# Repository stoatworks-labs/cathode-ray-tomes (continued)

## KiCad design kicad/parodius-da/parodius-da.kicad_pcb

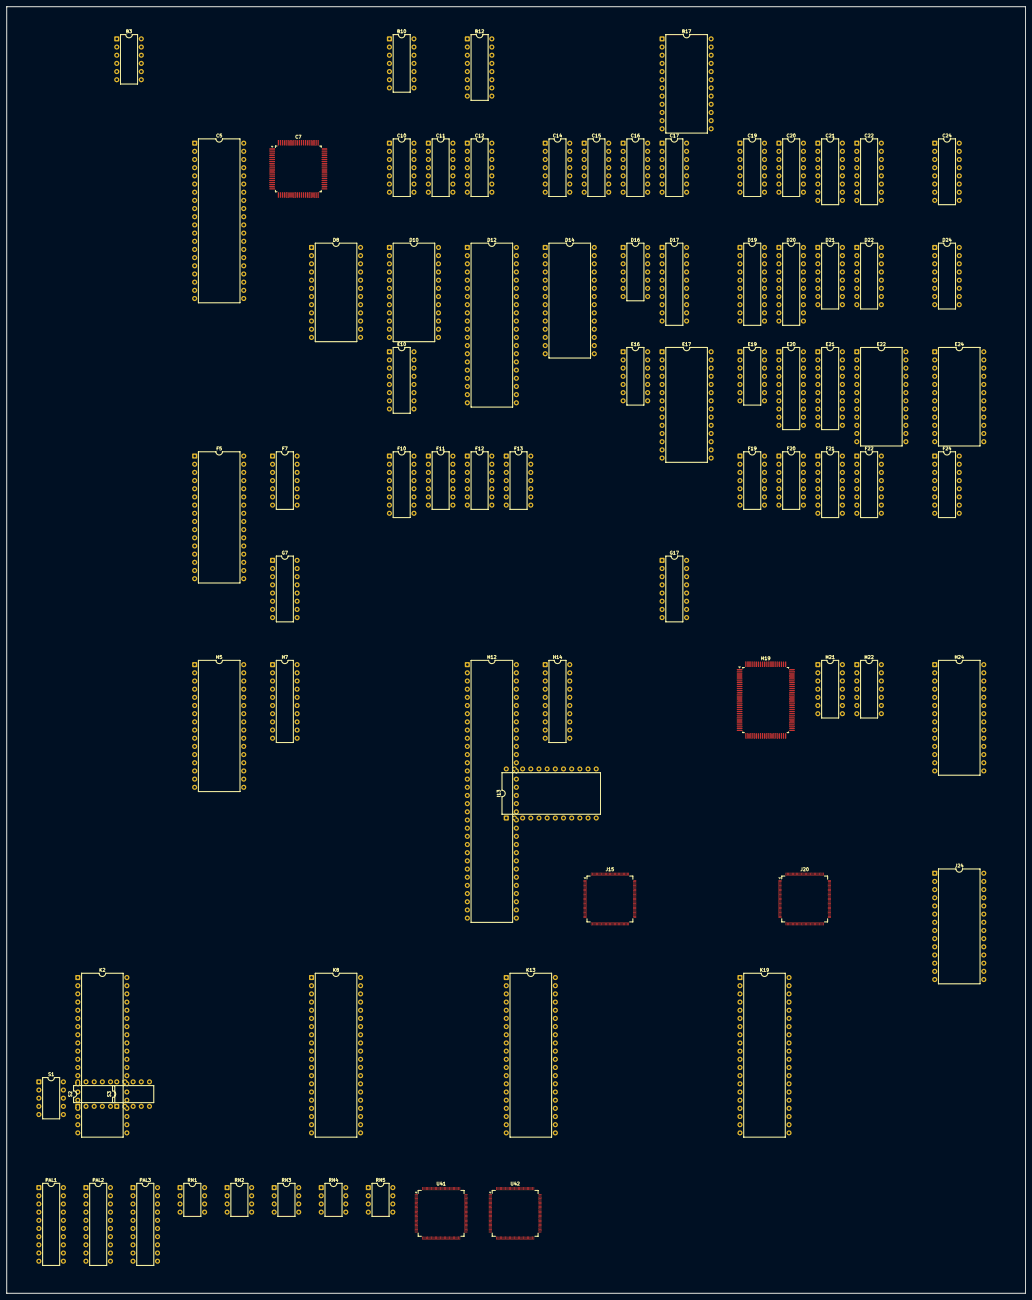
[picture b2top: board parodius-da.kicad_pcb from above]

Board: 2 copper layers, 316.5 x 399.7 mm, 79 parts (0 on the bottom side), 541 nets, no tracks yet.

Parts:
B3: MB3722; DIP-12_W7.62mm
B10: LM324; DIP-14_W7.62mm
B12: YM3012; DIP-16_W7.62mm
B17: 051550; DIP-24_W15.24mm
C5: 955D04; DIP-40_W15.24mm
C7: 053260; PQFP-80_14x14mm_P0.65mm
C10: 74LS32; DIP-14_W7.62mm
C11: 74LS74; DIP-14_W7.62mm
C12: 74LS20; DIP-14_W7.62mm
C14: 74LS04; DIP-14_W7.62mm
C15, C16, C17, C19, C20: 74LS07; DIP-14_W7.62mm
C21, C22, C24: 74LS253; DIP-16_W7.62mm
D8: YM2151; DIP-24_W15.24mm
D10: CY7C128-45PC; DIP-24_W15.24mm
D12: Z80CPU; DIP-40_W15.24mm
D14: 27C512; DIP-28_W15.24mm
D16: 74LS74; DIP-14_W7.62mm
D17, D19, D20: 74LS273; DIP-20_W7.62mm
D21: 74LS253; DIP-16_W7.62mm
D22, D24: 74LS257; DIP-16_W7.62mm
E10: 74LS139; DIP-16_W7.62mm
E16: 74LS00; DIP-14_W7.62mm
E17: MB8464A-10W-15W; DIP-28_W15.24mm
E19: 74LS07; DIP-14_W7.62mm
E20, E21: 74LS245; DIP-20_W7.62mm
E22, E24: HM6116P-3; DIP-24_W15.24mm
F5: 27C010; DIP-32_W15.24mm
F7: 74LS04; DIP-14_W7.62mm
F10: 74LS367; DIP-16_W7.62mm
F11: 74LS08; DIP-14_W7.62mm
F12, F13: 74LS32; DIP-14_W7.62mm
F19: 74LS74; DIP-14_W7.62mm
F20: 74LS164; DIP-14_W7.62mm
F21, F22, F24: 74LS157; DIP-16_W7.62mm
G7: 74LS174; DIP-16_W7.62mm
G17: 74LS157; DIP-16_W7.62mm
H5: 27C010; DIP-32_W15.24mm
H7, H14: 74LS245; DIP-20_W7.62mm
H12: 053248; DIP-64_W15.24mm
H19: 053251; PQFP-100_14x20mm_P0.65mm
H21: 74LS04; DIP-14_W7.62mm
H22: 74LS74; DIP-14_W7.62mm
H24: MB8464A-10W-15W; DIP-28_W15.24mm
I13: HM6116P-3; DIP-24_W15.24mm
J15: 051962; TQFP-120_14x14mm_P0.4mm
J20: 052109; TQFP-120_14x14mm_P0.4mm
J24: MB8464A-10W-15W; DIP-28_W15.24mm
K2, K8, K13, K19: 955D05-06-07-08; DIP-40_W15.24mm
PAL1, PAL2, PAL3: PAL16L8; DIP-20_W7.62mm
RN1, RN2, RN3, RN4, RN5: KONAMI_005273; DIP-8_W7.62mm
S1, S2, S3: 052535; DIP-10_W7.62mm
U41: 053245; TQFP-120_14x14mm_P0.4mm
U42: 053244; TQFP-120_14x14mm_P0.4mm

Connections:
/+12V: B3.10, B17.19
/AUX1: C7.23, D8.21
/COIN_CNT_1: B17.22, B17.23
/COIN_CNT_2: B17.20, B17.21
/CPU~EN: D22.2, F13.9, U41.26
/DFI0: H19.47, J15.59
/DFI1: H19.48, J15.60
/DFI2: H19.49, J15.62
/DFI3: H19.50, J15.63
/DFI5: H19.51, J15.65
/DFI6: H19.52, J15.66
/DFI7: H19.54, J15.67
/DSA0: H19.66, J15.46
/DSA1: H19.67, J15.47
/DSA2: H19.68, J15.48
/DSA3: H19.69, J15.49
/DSA5: H19.70, J15.51
/DSA6: H19.71, J15.52
/DSA7: H19.72, J15.53
/DSB0: H19.57, J15.30
/DSB1: H19.58, J15.32
/DSB2: H19.59, J15.33
/DSB3: H19.60, J15.34
/DSB5: H19.61, J15.36
/DSB6: H19.62, J15.37
/DSB7: H19.63, J15.38
/GM12: J15.95, U41.12, U42.12
/IOCS: D22.15, D24.15, PAL1.13
/M6: D16.3, D19.11, D20.11, F20.8, H19.41, J15.78, U41.10, U42.10
/M12: F19.3, H21.11, H21.13, J20.103
/MAIN_A0: C7.18, E17.10, F5.12, F7.5, F7.9, G17.11, H5.12, H12.14, H19.85, J15.88, J20.66, U41.9, U42.19
/MAIN_A1: E17.9, F5.11, F7.11, F24.2, H5.11, H12.13, H19.84, J15.89, J20.67, U41.25, U42.18
/MAIN_A2: E10.14, E17.8, F5.10, F24.5, H5.10, H12.12, H19.83, J20.68, U41.24, U42.17
/MAIN_A3: E10.13, E17.7, F5.9, F24.11, H5.9, H12.11, H19.82, J20.69, U41.23, U42.15
/MAIN_A4: E17.6, F5.8, F24.14, H5.8, H12.9, J20.116, PAL1.11, U41.22
/MAIN_A5: E17.5, F5.7, F22.2, H5.7, H12.8, J20.115, PAL1.9, U41.20
/MAIN_A6: E17.4, F5.6, F22.5, H5.6, H12.7, J20.114, PAL1.8, U41.19
/MAIN_A7: E17.3, F5.5, F22.11, H5.5, H12.6, J20.113, PAL1.5, U41.18
/MAIN_A8: E17.25, F5.27, F22.14, H5.27, H12.62, J20.112, PAL1.4, U41.17
/MAIN_A9: E17.24, F5.26, F21.2, H5.26, H12.61, J20.111, PAL1.3, U41.15
/MAIN_A10: E17.21, F5.23, F21.5, H5.23, H12.60, J20.110, PAL3.8, U41.14
/MAIN_A11: E17.23, F5.25, H5.25, H12.59, J20.109, PAL3.7
/MAIN_A12: E17.2, F5.4, H5.4, H12.56, J20.80, PAL3.6
/MAIN_A13: H12.55, J20.81, PAL2.5, PAL3.5
/MAIN_A14: H12.54, J20.82, PAL2.4, PAL3.4
/MAIN_A15: H12.53, J20.83, PAL2.3, PAL3.3
/MAIN_A16: H12.38, PAL2.9
/MAIN_A17: H12.39, PAL2.8
/MAIN_A18: H12.40, PAL2.7
/MAIN_A19: H12.41, PAL2.6
/MAIN_DB0: C7.8, C24.7, D17.3, D22.4, E17.11, E20.2, E21.2, G7.3, H7.2, H14.2, H19.80, J15.79, J20.56, U42.29
/MAIN_DB1: C7.9, C24.9, D17.4, D22.7, E17.12, E20.3, E21.3, G7.4, H7.3, H14.3, H19.79, J15.80, J20.57, U42.28
/MAIN_DB2: C7.10, C22.7, D17.7, D22.9, E17.13, E20.4, E21.4, G7.6, H7.4, H14.4, H19.77, J15.81, J20.58, U42.27
/MAIN_DB3: C7.11, C22.9, D17.8, D22.12, E17.15, E20.5, E21.5, H7.5, H14.5, H19.76, J15.82, J20.59, U42.26
/MAIN_DB4: C7.13, C21.7, D17.13, D24.4, E17.16, E20.6, E21.6, H7.6, H14.6, H19.75, J15.83, J20.60, U42.25
/MAIN_DB5: C7.14, C21.9, D17.14, D24.7, E17.17, E20.7, E21.7, G7.11, H7.7, H14.7, H19.74, J15.84, J20.62, U42.24
/MAIN_DB6: C7.15, D17.17, D21.7, D24.9, E17.18, E20.8, E21.8, G7.13, H7.8, J15.85, J20.63, U42.23
/MAIN_DB7: C7.16, D17.18, D21.9, D24.12, E17.19, E20.9, E21.9, G7.14, H7.9, H14.8, H14.9, J15.86, J20.64, U42.22
/MAIN~IRQ: H12.4, J20.87
/MBRIT0: D17.15, E16.5
/MBRIT1: D17.16, E16.13
/MBRIT2: D17.19, E16.2
/OBJPXL0: H19.30, U42.120
/OBJPXL1: H19.31, U42.119
/OBJPXL2: H19.32, U42.118
/OBJPXL3: H19.33, U42.117
/OBJPXL4: H19.34, U42.116
/OBJPXL5: H19.35, U42.115
/OBJPXL6: H19.36, U42.114
/OBJPXL7: H19.37, U42.113
/OBJPXL8: H19.38, U42.112
/PALETTE~CS: E20.1, E21.1, F11.5, F21.1, F21.14, F22.1, F24.1, G17.1, PAL3.14
/PAL_BANK: F21.11, G7.7
/PQ: F10.4, J20.89
/PR13: H19.25, U42.110
/PR14: H19.27, U42.109
/RMSCR~RD: D17.9, J15.96, J20.97, PAL1.2
/R/~W: C7.19, E17.27, F7.3, F12.2, F12.9, F12.13, H7.1, H12.15
/SCR_PE: F10.2, F19.11, J20.90
/SC~CS: C7.72, E10.6
/SDI0: H19.95, U42.108
/SH1: B12.6, C7.22, C11.11, D8.20
/SH2: B12.5, D8.19
/SND_A0: C7.70, D8.4, D10.8, D12.30, D14.10
/SND_A1: C7.69, D10.7, D12.31, D14.9
/SND_A2: C7.68, D10.6, D12.32, D14.8
/SND_A3: C7.67, D10.5, D12.33, D14.7
/SND_A4: C7.66, D10.4, D12.34, D14.6
/SND_A5: C7.65, D10.3, D12.35, D14.5
/SND_A6: D10.2, D12.36, D14.4
/SND_A7: D10.1, D12.37, D14.3
/SND_A8: D10.23, D12.38, D14.25
/SND_A9: D10.22, D12.39, D14.24, E10.2
/SND_A10: D10.19, D12.40, D14.21, E10.3
/SND_A11: C10.10, C14.1, D12.1, D14.23
/SND_A12: C12.5, D12.2, D14.2
/SND_A13: C12.4, D12.3, D14.26
/SND_A14: C12.2, D12.4, D14.27
/SND_A15: C12.1, D12.5, D14.1
/SND_D0: C7.5, D8.10, D10.9, D12.14, D14.11
/SND_D1: C7.4, D8.12, D10.10, D12.15, D14.12
/SND_D2: C7.3, D8.13, D10.11, D12.12, D14.13
/SND_D3: C7.2, D8.14, D10.13, D12.8, D14.15
/SND_D4: C7.1, D8.15, D10.14, D12.7, D14.16
/SND_D5: C7.80, D8.16, D10.15, D12.9, D14.17
/SND_D6: C7.79, D8.17, D10.16, D12.10, D14.18
/SND_D7: C7.78, D8.18, D10.17, D12.13, D14.19
/SO~CLK: B12.2, D8.23
/S~CLK: C7.21, D8.24, D12.6, F7.12
/S~RD: D8.6, D10.20, D12.21, D14.22, F7.1
/WD_OUT1: B17.15, D17.2
/WD_OUT2: B17.16, D17.5
/colmix/BRIT: D16.2, H19.88
/colmix/BRITEN: D16.5, E16.1, E16.4, E16.12
/colmix/CO1: F24.3, H19.19
/colmix/CO2: F24.6, H19.18
/colmix/CO3: F24.10, H19.17
/colmix/CO4: F24.13, H19.16
/colmix/CO5: F22.3, H19.14
/colmix/CO6: F22.6, H19.13
/colmix/CO7: F22.10, H19.12
/colmix/CO8: F22.13, H19.11
/colmix/CO9: F21.3, H19.93
/colmix/CO10: F21.6, H19.92
/colmix/CO11: F21.10, H19.91
/colmix/MCO1: E22.19, E24.8, F24.4
/colmix/MCO2: E22.8, E24.7, F24.7
/colmix/MCO3: E22.5, E24.6, F24.9
/colmix/MCO4: E22.4, E24.5, F22.4
/colmix/MCO5: E22.6, E24.4, F22.12
/colmix/MCO6: E22.7, E24.3, F21.7
/colmix/MCO7: E22.23, E24.2, F21.9
/colmix/MCO8: E22.22, E24.1, F24.12
/colmix/MCO9: E22.1, E24.23, F22.9
/colmix/MCO10: E22.2, E24.22, F21.4
/colmix/MCO11: E22.3, E24.19, F22.7
/colmix/MCO~OE: E22.20, E24.20, F21.12
/colmix/MCO~WRH: E24.21, F13.6
/colmix/MCO~WRL: E22.21, F13.3
/colmix/RGB0: D19.3, E21.18, E22.9
/colmix/RGB1: D19.4, E21.17, E22.10
/colmix/RGB2: D19.7, E21.16, E22.11
/colmix/RGB3: D19.8, E21.15, E22.13
/colmix/RGB4: D19.13, E21.14, E22.14
/colmix/RGB5: D19.14, E21.13, E22.15
/colmix/RGB6: D19.17, E21.12, E22.16
/colmix/RGB7: E21.11, E22.17
/colmix/RGB8: D20.3, E20.18, E24.9
/colmix/RGB9: D20.4, E20.17, E24.10
/colmix/RGB10: D20.7, E20.16, E24.11
/colmix/RGB11: D20.8, E20.15, E24.13
/colmix/RGB12: D20.13, E20.14, E24.14
/colmix/RGB13: D20.14, E20.13, E24.15
/colmix/RGB14: D20.17, E20.12, E24.16
/colmix/RGB15: D20.18, E20.11, E24.17
/colmix/SDO0: C14.5, H19.87
/colmix/rgb/B0: C17.5, D19.6
/colmix/rgb/B1: C16.11, D19.9
/colmix/rgb/B2: C16.9, D19.12
/colmix/rgb/B3: C15.9, D19.15
/colmix/rgb/B4: C15.11, D19.16
/colmix/rgb/G0: C17.9, D20.15
/colmix/rgb/G1: C19.3, D20.16
/colmix/rgb/G2: C20.13, D20.19
/colmix/rgb/G3: C19.5, D19.2
/colmix/rgb/G4: C17.3, D19.5
/colmix/rgb/R0: C20.9, D20.2
/colmix/rgb/R1: C20.1, D20.5
/colmix/rgb/R2: C20.5, D20.6
/colmix/rgb/R3: C20.3, D20.9
/colmix/rgb/R4: C20.11, D20.12
/colmix/rgb/~MBRIT0: E16.6, E19.1, E19.11, E19.13
/colmix/rgb/~MBRIT1: C19.1, C19.11, C19.13, E16.11
/colmix/rgb/~MBRIT2: C17.1, C17.11, C17.13, E16.3
/colmix/rgb/~SHADOW: C16.1, C16.3, C16.13, D19.19
/colmix/~COCEH: E20.19, F13.4, G17.12
/colmix/~COCEL: E21.19, F13.1, G17.9
/colmix/~CS: F12.11, H19.81
/io_cabinet/I1P_BTN_1: C21.13, RN5.5
/io_cabinet/I1P_BTN_2: D21.3, RN1.1
/io_cabinet/I1P_BTN_3: D21.13, RN1.5
/io_cabinet/I1P_DOWN: C22.3, RN3.1
/io_cabinet/I1P_LEFT: C22.13, RN3.5
/io_cabinet/I1P_RIGHT: C21.3, RN5.1
/io_cabinet/I1P_START: C24.3, RN2.1
/io_cabinet/I1P_UP: C24.13, RN2.5
/io_cabinet/I2P_BTN_1: C21.12, RN5.7
/io_cabinet/I2P_BTN_2: D21.4, RN1.3
/io_cabinet/I2P_BTN_3: D21.12, RN1.7
/io_cabinet/I2P_DOWN: C22.4, RN3.3
/io_cabinet/I2P_LEFT: C22.12, RN3.7
/io_cabinet/I2P_RIGHT: C21.4, RN5.3
/io_cabinet/I2P_START: C24.4, RN2.3
/io_cabinet/I2P_UP: C24.12, RN2.7
/io_cabinet/ICOIN_1: C22.5, RN4.5
/io_cabinet/ICOIN_2: C22.11, RN4.7
/io_cabinet/ISERVICE1: C24.5, RN4.1
/io_cabinet/ISERVICE2: C24.11, RN4.3
/io_cabinet/~A0: C21.14, C22.14, C24.14, D21.14, D22.1, D24.1, F7.6
/io_cabinet/~A1: C21.2, C22.2, C24.2, D21.2, F7.10
/main/AS: F19.4, F19.10, H21.4, H22.1
/main/BANK1: G7.5, PAL3.9
/main/BANKR: D17.12, PAL3.2
/main/BANK~CS: E10.11, G7.9
/main/DTAC: F11.6, H12.49
/main/GND: F5.16, H5.16, PAL1.10
/main/MAIN_A20: H12.43, PAL2.18
/main/MAIN_D0: F5.13, H5.13, H7.18, H12.21
/main/MAIN_D1: F5.14, H5.14, H7.17, H12.22
/main/MAIN_D2: F5.15, H5.15, H7.16, H12.23
/main/MAIN_D3: F5.17, H5.17, H7.15, H12.24
/main/MAIN_D4: F5.18, H5.18, H7.14, H12.27
/main/MAIN_D5: F5.19, H5.19, H7.13, H12.28
/main/MAIN_D6: F5.20, H5.20, H7.12, H12.29
/main/MAIN_D7: F5.21, H5.21, H7.11, H12.30
/main/MAIN~CLK: H12.18, H21.12
/main/MAIN~RST: F10.7, H12.2
/main/MISC: E10.15, PAL1.14
/main/MPQ: F10.5, H12.17
/main/NC: PAL2.1, PAL3.18
/main/PE: F10.3, H12.51
/main/PROG_A13: F5.28, H5.28, PAL2.12
/main/PROG_A14: F5.29, H5.29, PAL2.13
/main/PROG_A15: F5.3, H5.3, PAL2.14
/main/PROG_A16: F5.2, H5.2, PAL2.15
/main/WORK~CS: E17.20, PAL3.16
/main/~AS: F19.12, H12.16, H21.3, PAL3.1
/main/~M12: H21.10, H22.3
/main/~PAGED: E16.10, PAL2.11, PAL3.17
/main/~PROGCS1: F5.24, PAL2.17
/main/~PROGCS2: E16.9, H5.24, PAL2.16
/main/~UNPAGED: PAL2.2, PAL3.19
/main/~WRK: G7.2, PAL3.11
/main/~i6: PAL1.6, PAL3.13
/main/~i7: PAL1.7, PAL3.12
/objects/AR0: U41.119, U42.30
/objects/AR1: U41.118, U42.32
/objects/AR2: U41.117, U42.33
/objects/AROK: U41.116, U42.34
/objects/BR0: U41.115, U42.35
/objects/BR1: U41.114, U42.36
/objects/BR2: U41.113, U42.37
/objects/BROK: U41.112, U42.38
/objects/CLAT: U41.86, U42.64
/objects/HP0: U41.96, U42.54
/objects/HP1: U41.97, U42.53
/objects/HP2: U41.98, U42.52
/objects/HP3: U41.99, U42.50
/objects/HP4: U41.100, U42.49
/objects/HP5: U41.102, U42.48
/objects/HP6: U41.103, U42.47
/objects/HP7: U41.104, U42.45
/objects/HP8: U41.105, U42.44
/objects/HP9: U41.107, U42.43
/objects/HRFP: U41.110, U42.39
/objects/OBJRAMD0: H14.18, I13.9, U41.45
/objects/OBJRAMD1: H14.17, I13.10, U41.44
/objects/OBJRAMD2: H14.16, I13.11, U41.43
/objects/OBJRAMD3: H14.15, I13.13, U41.42
/objects/OBJRAMD4: H14.14, I13.14, U41.40
/objects/OBJRAMD5: H14.13, I13.15, U41.39
/objects/OBJRAMD6: H14.12, I13.16, U41.38
/objects/OBJRAMD7: H14.11, I13.17, U41.37
/objects/OBJROMA0: K2.9, K8.9, U41.85
/objects/OBJROMA1: K2.8, K8.8, U41.84
/objects/OBJROMA2: K2.7, K8.7, U41.83
/objects/OBJROMA3: K2.6, K8.6, U41.82
/objects/OBJROMA4: K2.5, K8.5, U41.80
/objects/OBJROMA5: K2.4, K8.4, U41.79
/objects/OBJROMA6: K2.3, K8.3, U41.78
/objects/OBJROMA7: K2.2, K8.2, U41.77
/objects/OBJROMA8: K2.40, K8.40, U41.75
/objects/OBJROMA9: K2.39, K8.39, U41.74
/objects/OBJROMA10: K2.38, K8.38, U41.73
/objects/OBJROMA11: K2.37, K8.37, U41.72
/objects/OBJROMA12: K2.36, K8.36, U41.70
/objects/OBJROMA13: K2.35, K8.35, U41.69
/objects/OBJROMA14: K2.34, K8.34, U41.68
/objects/OBJROMA15: K2.33, K8.33, U41.67
/objects/OBJROMA16: K2.32, K8.32, U41.66
/objects/OBJROMA17: K2.1, K8.1, U41.65
/objects/OBJROMD0: K2.13, U42.100
/objects/OBJROMD1: K2.15, U42.99
/objects/OBJROMD2: K2.17, U42.98
/objects/OBJROMD3: K2.19, U42.97
/objects/OBJROMD4: K2.22, U42.96
/objects/OBJROMD5: K2.24, U42.95
/objects/OBJROMD6: K2.26, U42.94
/objects/OBJROMD7: K2.28, U42.93
/objects/OBJROMD8: K2.14, U42.92
/objects/OBJROMD9: K2.16, U42.90
/objects/OBJROMD10: K2.18, U42.89
/objects/OBJROMD11: K2.20, U42.88
/objects/OBJROMD12: K2.23, U42.87
/objects/OBJROMD13: K2.25, U42.86
/objects/OBJROMD14: K2.27, U42.85
/objects/OBJROMD15: K2.29, U42.84
/objects/OBJROMD16: K8.13, U42.83
/objects/OBJROMD17: K8.15, U42.82
/objects/OBJROMD18: K8.17, U42.80
/objects/OBJROMD19: K8.19, U42.79
/objects/OBJROMD20: K8.22, U42.78
/objects/OBJROMD21: K8.24, U42.77
/objects/OBJROMD22: K8.26, U42.75
/objects/OBJROMD23: K8.28, U42.74
/objects/OBJROMD24: K8.14, U42.73
/objects/OBJROMD25: K8.16, U42.72
/objects/OBJROMD26: K8.18, U42.70
/objects/OBJROMD27: K8.20, U42.69
/objects/OBJROMD28: K8.23, U42.68
/objects/OBJROMD29: K8.25, U42.67
/objects/OBJROMD30: K8.27, U42.66
/objects/OBJROMD31: K8.29, U42.65
/objects/ORAMA0: I13.3, U41.50
/objects/ORAMA1: I13.4, U41.52
/objects/ORAMA2: I13.5, U41.53
/objects/ORAMA3: I13.23, U41.54
/objects/ORAMA4: I13.6, U41.55
/objects/ORAMA5: I13.22, U41.56
/objects/ORAMA6: I13.7, U41.57
/objects/ORAMA7: I13.8, U41.58
/objects/ORAMA8: I13.19, U41.59
/objects/ORAMA9: I13.2, U41.62
/objects/ORAMA10: I13.1, U41.63
/objects/PL0: U41.87, U42.63
/objects/PL1: U41.88, U42.62
/objects/PL2: U41.89, U42.60
/objects/PL3: U41.90, U42.59
/objects/PL4: U41.92, U42.58
/objects/PL5: U41.93, U42.57
/objects/PL6: U41.94, U42.56
/objects/SHADOW: U41.95, U42.55
/objects/~HIT: U41.108, U42.42
/objects/~OBJRAM_RD: F13.11, H14.1
/objects/~ZLD: U41.109, U42.40
/pcm/RA0: C5.29, C7.39
/pcm/RA1: C5.9, C7.40
/pcm/RA2: C5.8, C7.41
/pcm/RA3: C5.7, C7.42
/pcm/RA4: C5.6, C7.44
/pcm/RA5: C5.5, C7.45
/pcm/RA6: C5.4, C7.46
/pcm/RA7: C5.3, C7.47
/pcm/RA8: C5.2, C7.48
/pcm/RA9: C5.40, C7.49
/pcm/RA10: C5.39, C7.50
/pcm/RA11: C5.38, C7.51
/pcm/RA12: C5.37, C7.53
/pcm/RA13: C5.36, C7.54
/pcm/RA14: C5.35, C7.55
/pcm/RA15: C5.34, C7.56
/pcm/RA16: C5.33, C7.57
/pcm/RA17: C5.32, C7.58
/pcm/RA18: C5.1, C7.59
/pcm/RD0: C5.13, C7.29
/pcm/RD1: C5.15, C7.30
/pcm/RD2: C5.17, C7.31
/pcm/RD3: C5.19, C7.32
/pcm/RD4: C5.22, C7.35
/pcm/RD5: C5.24, C7.36
/pcm/RD6: C5.26, C7.37
/pcm/RD7: C5.28, C7.38
/scroll/COL5: J15.109, J20.42
/scroll/COL6: J15.108, J20.43
/scroll/COL7: J15.107, J20.46
/scroll/GFXROMA0: J20.35, K13.9, K19.9
/scroll/GFXROMA1: J20.34, K13.8, K19.8
/scroll/GFXROMA2: J20.33, K13.7, K19.7
/scroll/GFXROMA3: J20.32, K13.6, K19.6
/scroll/GFXROMA4: J20.30, K13.5, K19.5
/scroll/GFXROMA5: J20.29, K13.4, K19.4
/scroll/GFXROMA6: J20.28, K13.3, K19.3
/scroll/GFXROMA7: J20.27, K13.2, K19.2
/scroll/GFXROMA8: J20.26, K13.40, K19.40
/scroll/GFXROMA9: J20.25, K13.39, K19.39
/scroll/GFXROMA10: J20.24, K13.38, K19.38
/scroll/GFXROMA11: J20.37, K13.37, K19.37
/scroll/GFXROMA12: J20.38, K13.36, K19.36
/scroll/GFXROMA13: J20.41, K13.35, K19.35
/scroll/GFXROMA14: J20.39, K13.34, K19.34
/scroll/GFXROMA15: J20.40, K13.33, K19.33
/scroll/GFXROMA16: J20.23, K13.32, K19.32
/scroll/GFXROMA17: J20.22, K13.1, K19.1
/scroll/GFXROMD0: J15.29, K13.13
/scroll/GFXROMD1: J15.28, K13.15
/scroll/GFXROMD2: J15.27, K13.17
/scroll/GFXROMD3: J15.26, K13.19
/scroll/GFXROMD4: J15.25, K13.22
/scroll/GFXROMD5: J15.24, K13.24
/scroll/GFXROMD6: J15.23, K13.26
/scroll/GFXROMD7: J15.22, K13.28
/scroll/GFXROMD8: J15.21, K13.14
/scroll/GFXROMD9: J15.20, K13.16
/scroll/GFXROMD10: J15.19, K13.18
/scroll/GFXROMD11: J15.18, K13.20
/scroll/GFXROMD12: J15.17, K13.23
/scroll/GFXROMD13: J15.16, K13.25
/scroll/GFXROMD14: J15.13, K13.27
/scroll/GFXROMD15: J15.12, K13.29
/scroll/GFXROMD16: J15.11, K19.13
/scroll/GFXROMD17: J15.10, K19.15
/scroll/GFXROMD18: J15.9, K19.17
/scroll/GFXROMD19: J15.8, K19.19
/scroll/GFXROMD20: J15.7, K19.22
/scroll/GFXROMD21: J15.6, K19.24
/scroll/GFXROMD22: J15.5, K19.26
/scroll/GFXROMD23: J15.4, K19.28
/scroll/GFXROMD24: J15.3, K19.14
/scroll/GFXROMD25: J15.2, K19.16
/scroll/GFXROMD26: J15.120, K19.18
/scroll/GFXROMD27: J15.119, K19.20
/scroll/GFXROMD28: J15.118, K19.23
/scroll/GFXROMD29: J15.117, K19.25
/scroll/GFXROMD30: J15.116, K19.27
/scroll/GFXROMD31: J15.115, K19.29
/scroll/M24: H21.6, J15.90, J20.65
/scroll/SCRAMA0: H24.10, J20.2, J24.10
/scroll/SCRAMA1: H24.9, J20.120, J24.9
/scroll/SCRAMA2: H24.8, J20.119, J24.8
/scroll/SCRAMA3: H24.7, J20.118, J24.7
/scroll/SCRAMA4: H24.6, J20.117, J24.6
/scroll/SCRAMA5: H24.5, J20.70, J24.5
/scroll/SCRAMA6: H24.4, J20.71, J24.4
/scroll/SCRAMA7: H24.3, J20.72, J24.3
/scroll/SCRAMA8: H24.25, J20.73, J24.25
/scroll/SCRAMA9: H24.24, J20.76, J24.24
/scroll/SCRAMA10: H24.21, J20.77, J24.21
/scroll/SCRAMA11: H24.23, J20.78, J24.23
/scroll/SCRAMA12: H24.2, J20.79, J24.2
/scroll/VD0: H24.11, J20.20
/scroll/VD1: H24.12, J20.19
/scroll/VD2: H24.13, J20.18
/scroll/VD3: H24.15, J20.17
/scroll/VD4: H24.16, J20.16
/scroll/VD5: H24.17, J20.13
/scroll/VD6: H24.18, J20.12
/scroll/VD7: H24.19, J20.11
/scroll/VD8: J20.10, J24.11
/scroll/VD9: J20.9, J24.12
/scroll/VD10: J20.8, J24.13
/scroll/VD11: J20.7, J24.15
/scroll/VD12: J20.6, J24.16
/scroll/VD13: J20.5, J24.17
/scroll/VD14: J20.4, J24.18
/scroll/VD15: J20.3, J24.19
/scroll/ZA1H: J15.101, J20.50
/scroll/ZA2H: J15.100, J20.51
/scroll/ZA4H: J15.99, J20.52
/scroll/ZB1H: J15.106, J20.47
/scroll/ZB2H: J15.103, J20.48
/scroll/ZB4H: J15.102, J20.49
/scroll/~BE: J15.98, J20.53
/scroll/~RCS1: J20.93, J24.20
/scroll/~ROE1: J20.95, J24.22
/scroll/~ROE2: H24.22, J20.96
/scroll/~RWE1: J20.107, J24.27
/scroll/~RWE2: H24.27, J20.108
/sound/SND~E: C10.11, E10.1
/sound/SRAM~CE: C10.8, D10.18
/sound/SROM~CE: C14.8, D14.20
/sound/S~IORQ: D12.20, F11.2
/sound/S~MREQ: C10.5, D12.19
/sound/S~WR: D8.5, D10.21, D12.22
/sound/~RFSH: C14.13, D12.28
/sound/~SET: C11.10, E10.5
/~HBLANK: F20.2, J15.70
/~HSYNC: J15.73, U41.4, U42.8
/~JOYSTK: C21.1, C21.15, C22.1, C22.15, C24.1, C24.15, D21.1, D21.15, PAL1.12
/~MDS: F13.2, F13.5, H12.20, U42.14
/~OBJRAM_CS: F11.12, F12.10, PAL3.15
/~OBJSET: C14.11, F11.13, PAL1.17, U41.6, U42.13
/~OUTCS: E10.12, F12.1, F12.4
/~PCU_CS: F12.12, PAL1.16
/~RCS0: J20.92, U41.3, U42.3
/~RD: E17.22, F7.4, F12.5, F13.12, J15.87, J20.85, U41.13, U42.20
/~RESET: D17.1, F10.6, G7.1, J20.98
/~SOON: D16.11, E10.10
/~SOREG: C7.17, E10.9
/~VBLANK: F20.1, J15.69
/~VCS: H22.2, J15.97, J20.54, J20.84, PAL1.18
/~VSYNC: J15.72, U41.5, U42.9
/~WDOGRST: B12.7, C7.75, C11.13, D8.3, D12.26, F11.1, F20.9, H22.9, J15.92, J20.55
/~WDRST: B17.10, H22.12, H22.13
unnamed: B10.3, B12.15
unnamed: B10.2, B12.14
unnamed: B10.5, B12.9
unnamed: B10.6, B10.7
unnamed: B10.10, B12.12
unnamed: B10.8, B10.9
unnamed: B10.12, B12.10
unnamed: B10.13, B10.14
unnamed: B10.1, B12.13
unnamed: B17.1, F12.6
unnamed: C7.71, F7.2
unnamed: C10.1, C14.12
unnamed: C10.2, C12.6, C14.9
unnamed: C10.3, C10.4
unnamed: C10.6, C10.9, C10.12
unnamed: C10.13, C14.2
unnamed: C11.9, D12.17
unnamed: C14.10, F13.13
unnamed: D8.7, E10.4
unnamed: D12.16, D16.8
unnamed: D16.13, F11.3
unnamed: D17.11, F12.3
unnamed: C14.6, D19.18
unnamed: F11.11, F13.10
unnamed: F11.8, F19.2
unnamed: F11.4, F19.5
unnamed: F11.9, F19.9
unnamed: C15.1, C15.3, C15.13, F20.5
unnamed: F7.8, G17.14
unnamed: H21.1, H21.5
unnamed: E16.8, H7.19
unnamed: F13.8, H14.19
unnamed: F11.10, H22.6
unnamed: H21.2, H22.11
unnamed: I13.20, U41.49
unnamed: I13.21, U41.47
unnamed: C15.5, J15.76
unnamed: C15.2, S1.7
unnamed: C17.6, S1.6
unnamed: C16.10, S1.5
unnamed: C16.8, S1.4
unnamed: C15.8, S1.3
unnamed: C15.10, S1.2
unnamed: C15.12, S2.7
unnamed: C17.8, S2.6
unnamed: C19.4, S2.5
unnamed: C20.12, S2.4
unnamed: C19.6, S2.3
unnamed: C17.4, S2.2
unnamed: C15.4, S3.7
unnamed: C20.8, S3.6
unnamed: C20.2, S3.5
unnamed: C20.6, S3.4
unnamed: C20.4, S3.3
unnamed: C20.10, S3.2
unnamed: F12.8, U41.7
VCC: B10.4, B12.1, B17.9, C5.21, C7.20, C7.33, C7.73, C10.14, C11.14, C12.14, C14.14, C15.14, C16.14, C17.14, C19.14, C20.14, C21.16, C22.16, C24.16, D8.22, D10.24, D12.11, D14.28, D16.1, D16.4, D16.10, D16.12, D16.14, D19.1, D20.1, D21.16, D24.2, D24.5, D24.11, D24.14, E10.16, E16.14, E17.26, E17.28, E19.14, E22.24, E24.24, F5.1, F5.31, F5.32, F7.14, F10.16, F11.14, F12.14, F13.14, F19.1, F19.13, F19.14, F20.14, G7.16, G17.10, G17.13, H5.1, H5.31, H5.32, H12.26, H12.50, H12.58, H19.1, H19.2, H19.3, H19.28, H19.29, H19.39, H19.42, H19.43, H19.44, H19.45, H19.46, H19.53, H19.78, H19.97, H19.98, H19.99, H19.100, H21.14, H22.4, H22.10, H22.14, H24.26, H24.28, I13.24, J15.14, J15.44, J15.74, J15.104, J20.14, J20.44, J20.74, J20.104, J24.26, J24.28, K2.21, K2.31, K8.21, K8.31, K13.21, K13.31, K19.21, K19.31, PAL1.1, PAL1.20, PAL2.20, PAL3.20, S1.1, S2.1, S3.1, U41.16, U41.46, U41.60, U41.76, U41.106, U41.120, U42.16, U42.46, U42.76, U42.106
VSS: B3.6, B3.7, B10.11, B12.3, B12.8, B12.16, B17.13, B17.14, C5.10, C5.11, C5.12, C5.30, C5.31, C7.12, C7.34, C7.43, C7.52, C7.61, C7.74, C10.7, C11.7, C11.12, C12.7, C14.7, C15.7, C16.7, C17.7, C19.7, C20.7, C21.8, C22.8, C24.8, D8.1, D8.11, D10.12, D12.29, D14.14, D16.7, D21.8, D22.3, D24.6, E10.8, E16.7, E17.14, E19.7, E22.12, E22.18, E24.12, E24.18, F5.22, F7.7, F10.1, F10.8, F11.7, F12.7, F13.7, F19.7, F20.7, F21.13, F21.15, F22.15, F24.15, G7.8, G17.15, H5.22, H12.1, H12.5, H12.10, H12.19, H12.25, H12.31, H12.32, H12.33, H12.34, H12.35, H12.36, H12.37, H12.42, H12.47, H12.48, H12.52, H12.57, H19.4, H19.5, H19.6, H19.7, H19.8, H19.9, H19.10, H19.15, H19.20, H19.21, H19.22, H19.23, H19.24, H19.40, H19.55, H19.56, H19.64, H19.65, H19.73, H19.90, H19.94, H19.96, H21.7, H22.7, H24.14, H24.20, I13.12, I13.18, J15.1, J15.15, J15.31, J15.45, J15.61, J15.75, J15.91, J15.94, J15.105, J15.110, J15.111, J15.112, J15.113, J20.1, J20.15, J20.21, J20.31, J20.45, J20.61, J20.75, J20.91, J20.105, J24.14, K2.10, K2.11, K2.12, K2.30, K8.10, K8.11, K8.12, K8.30, K13.10, K13.11, K13.12, K13.30, K19.10, K19.11, K19.12, K19.30, PAL2.10, PAL3.10, S1.9, S2.9, S3.9, U41.1, U41.2, U41.8, U41.11, U41.21, U41.31, U41.41, U41.51, U41.61, U41.71, U41.81, U41.91, U41.101, U41.111, U42.1, U42.2, U42.11, U42.21, U42.31, U42.41, U42.51, U42.61, U42.71, U42.81, U42.91, U42.101, U42.111
